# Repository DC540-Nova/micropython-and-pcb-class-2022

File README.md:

# MicroPython & PCB Class 2022
MicroPython & PCB Class 2022 repo.

<br>

# Prerequisites (ideally before class starts)
* Install Thonny
* Install Kicad 6 -- follow through their installation procedure to make sure you have symbol and footprint libraries. Hit us up in the Discord class channel if you have any issues.

# Parts (Amazon links are Amazon Associate Links, purchasing through these links Benefits DC540)
[Raspberry Pi Pico w/ Pre-Soldered Headers](https://www.amazon.com/Raspberry-Microcontroller-Development-Dual-Core-Processor/dp/B08TN4VLN7?crid=13SC9RF6AR4FG&keywords=raspberry+pi+pico&qid=1661530301&sprefix=raspberry+pi+pico,aps,98&sr=8-11&linkCode=sl1&tag=540baab-20&linkId=3f7a7fddf92c960705a15b6c127fc1d6&language=en_US&ref_=as_li_ss_tl)<br>
[Breadboard & Wires](https://amzn.to/3LBkxHO) [updated link 2022-09-21] <br>
[Push Buttons](https://www.amazon.com/QTEATAK-Momentary-Tactile-Button-Switch/dp/B07VSNN9S2?crid=397PJODSKLVT8&keywords=5mm+4-post+push+button&qid=1661556619&sprefix=5mm+4-post+push+button,aps,43&sr=8-8&linkCode=sl1&tag=540baab-20&linkId=967552c52062183be0af39d3209359f7&language=en_US&ref_=as_li_ss_tl)<br>
[NeoPixel Ring](https://www.amazon.com/Stemedu-WS2812B-Integrated-Drivers-Raspberry/dp/B09MHX78WL?crid=2C4AG9RZT6W9J&keywords=neopixel%2Bring&qid=1661976974&s=hi&sprefix=neopixel%2Bring,tools,54&sr=1-4&th=1&linkCode=sl1&tag=540baab-20&linkId=e2077e5200e67458f7c71553bfc39023&language=en_US&ref_=as_li_ss_tl)<br>
[SSD1306 Display](https://www.amazon.com/HiLetgo-Serial-128X64-Display-Color/dp/B06XRBTBTB?crid=H7MU2U37O3GF&keywords=ssd1306+oled+display&qid=1661556692&sprefix=ssd1306,aps,72&sr=8-9&linkCode=sl1&tag=540baab-20&linkId=b2929946a48e2fb56bf9353001b6bba1&language=en_US&ref_=as_li_ss_tl)<br>

# Lesson Playlist
### [YouTube](https://youtube.com/playlist?list=PLvHfoRwREM9NEh0unEx78AdT5MzEejzg7)

<br>

# License
[Apache License, Version 2.0](https://www.apache.org/licenses/LICENSE-2.0)

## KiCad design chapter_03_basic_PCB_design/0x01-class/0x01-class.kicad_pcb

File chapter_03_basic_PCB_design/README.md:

# MicroPython & PCB Class 2022
MicroPython & PCB Class 2022 Chapter 3 - Basic PCB Design.

<br>

## PREREQUISITE - WATCH LESSON 3 [video](https://www.youtube.com/watch?v=9N72FxIyK1k)

<br>

# STEP 1: Create Project
```bash
file
new project
0x01-class
SAVE
```

# STEP 2: Open Schematic
```bash
double-click 0x01-class-kicad_sch
visit https://github.com/ncarandini/KiCad-RP-Pico
code
download ZIP
(unzip file)
```

# STEP 3: Add Pico Footprint To SCH
```bash
create, delete and edit footprints
file
add library
global
KiCad-RP-Pico-main
RP-Pico Libraries
MCU_RapsberryPi_and_Boards.kicad_sym
select folder
```

# STEP 4: Place Pico Footprint
```bash
place
add symbol [a]
(search) Pico
MCU_RapsberryPi_and_Boards
Pico
OK
```

# STEP 5: Place NeoPixel Footprints
```bash
place
add symbol [a]
(search) WS2812B
LED
WS2812B
OK
(hover over WS2812B, click and CTRL-C and CTRL-V)
(repeat 5x and place)
```

# STEP 6: Add A Power Port & Net Label
```bash
add a power port [p]
(search) +3V3
power
+3V3
OK
add a net label [l]
3V3
OK
(attach to wire hole on +3V3)
(click 3V3)
(click [m])
(attach to 3V3 on Pico)
(delete +3V3 and optional wire)
(hover over 3V3 on Pico, click and CTRL-C and CTRL-V)
(attach to wire hole on 1st WS2812B's VDD and repeat 5x for other WS2812B's)
```

# STEP 7: Add GND Net Label & Wire Up GND's To Neopixels
```bash
add a net label [l]
GND
OK
(attach to GND Pin 38 on Pico)
(hover over GND on Pico, click and CTRL-C and CTRL-V)
(attach to other GND pins on Pico, [r] when necessary)
(hover over any GND on Pico, click and CTRL-C and CTRL-V)
(attach to wire hole on 1st WS2812B's VSS and repeat 5x for other WS2812B's)
```

# STEP 8: Add NeoPixel Net Label & Wire Up Neopixels
```bash
add a net label [l]
NP
OK
(attach to GPIO18 on Pico)
(hover over NP and CTRL-C and CTRL-V 1x)
(hover over NP and CTRL-C and CTRL-V 1x)
(type [r] 2x and attach to DIN hole on 1st WS2812B)
add a wire [w]
(attach to DOUT on 1st WS2812B and connect to DIN on 2nd WS2812B)
(repeat process to remainder of WS2812B's)
```

# STEP 9: Add Pico Footprint To PCB
```bash
open PCB in board editor
update PCB with changes made to schematic [F8]
annotate
update PCB
close
create, delete and edit footprints
file
add library
global
KiCad-RP-Pico-main
RP-Pico Libraries
MCU_RapsberryPi_and_Boards.pretty
select folder
(search) RPi_Pico_SMD_TH
(double-click)
(save)
(X)
```

# STEP 10: Place Pico Footprint
```bash
open schematic in eeschema
(right-click inside empty area in Pico and click properties)
(click footprint RPi_Pico-RPi_Pico_SMD_TH and click bookshelf icon and ok)
(search) MCU_RaspberryPi_and_Boards
(double-click) RPi_Pico_SMD_TH
OK
open PCB in board editor
update PCB with changes made to schematic [F8]
update PCB
close
```

# STEP 11: Connect & Arrage Neopixels 
```bash
(arrange WS2812B's appropriately where GP18 connects to 1st WS2812B's NP, etc)
([r] when necessary)
(*NOTE: click in black area in center of WS2812B to move whole unit rather than pieces*)
edit board setup including layers, design rules and various defaults
design rules
net classes
+
PWR
track width
0.35 mm
net
/3V3
net class
PWR
/GND
net class
PWR
OK
```

# STEP 12: Route Tracks & Check Design
```
route tracks [x]
(click GP18 on Pico and conect to NP on first WS2812B)
(connect 2nd to 3rd, etc)
(click 3V3 on Pico and connect to 3V3 on first WS2812B)
(connect 2nd to 3rd, etc)
edge cuts
draw a rectangle
(draw box around circuit)
F.Cu
add a filled zone [CTRL-SHIFT-Z]
(click) /GND
ok
(draw ouside board trace, click upper left and drag and click as appropriate)
(double-click to finish)
fill all zones [b]
show the design rules checker window
run DRC
close
```

<br>

# License
[Apache License, Version 2.0](https://www.apache.org/licenses/LICENSE-2.0)

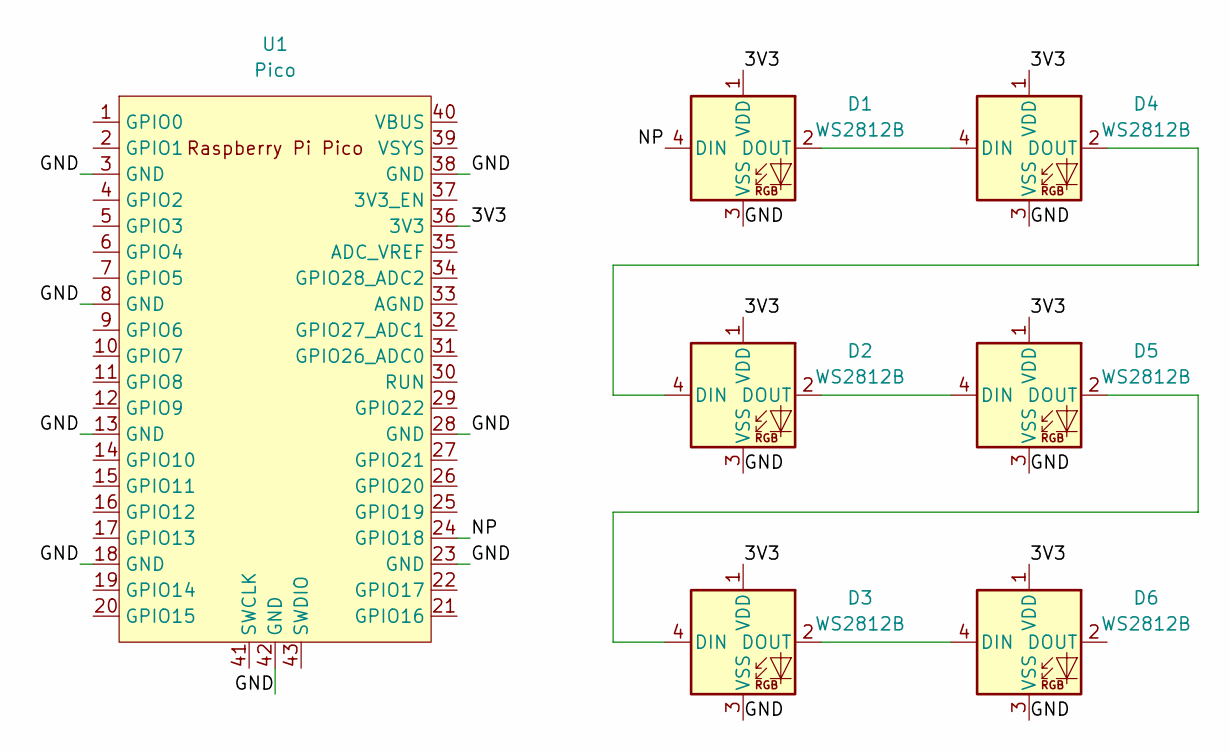
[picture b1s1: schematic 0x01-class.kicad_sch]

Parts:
D1, D2, D3, D4, D5, D6: WS2812B; LED_WS2812B_PLCC4_5.0x5.0mm_P3.2mm
U1: Pico; RPi_Pico_SMD_TH

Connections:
/3V3: D1.1 (VDD), D2.1 (VDD), D3.1 (VDD), D4.1 (VDD), D5.1 (VDD), D6.1 (VDD), U1.36 (3V3)
/GND: D1.3 (VSS), D2.3 (VSS), D3.3 (VSS), D4.3 (VSS), D5.3 (VSS), D6.3 (VSS), U1.3 (GND), U1.8 (GND), U1.13 (GND), U1.18 (GND), U1.23 (GND), U1.28 (GND), U1.38 (GND), U1.42 (GND)
/NP: D1.4 (DIN), U1.24 (GPIO18)
unnamed: D1.2 (DOUT), D4.4 (DIN)
unnamed: D2.2 (DOUT), D5.4 (DIN)
unnamed: D2.4 (DIN), D4.2 (DOUT)
unnamed: D3.2 (DOUT), D6.4 (DIN)
unnamed: D3.4 (DIN), D5.2 (DOUT)

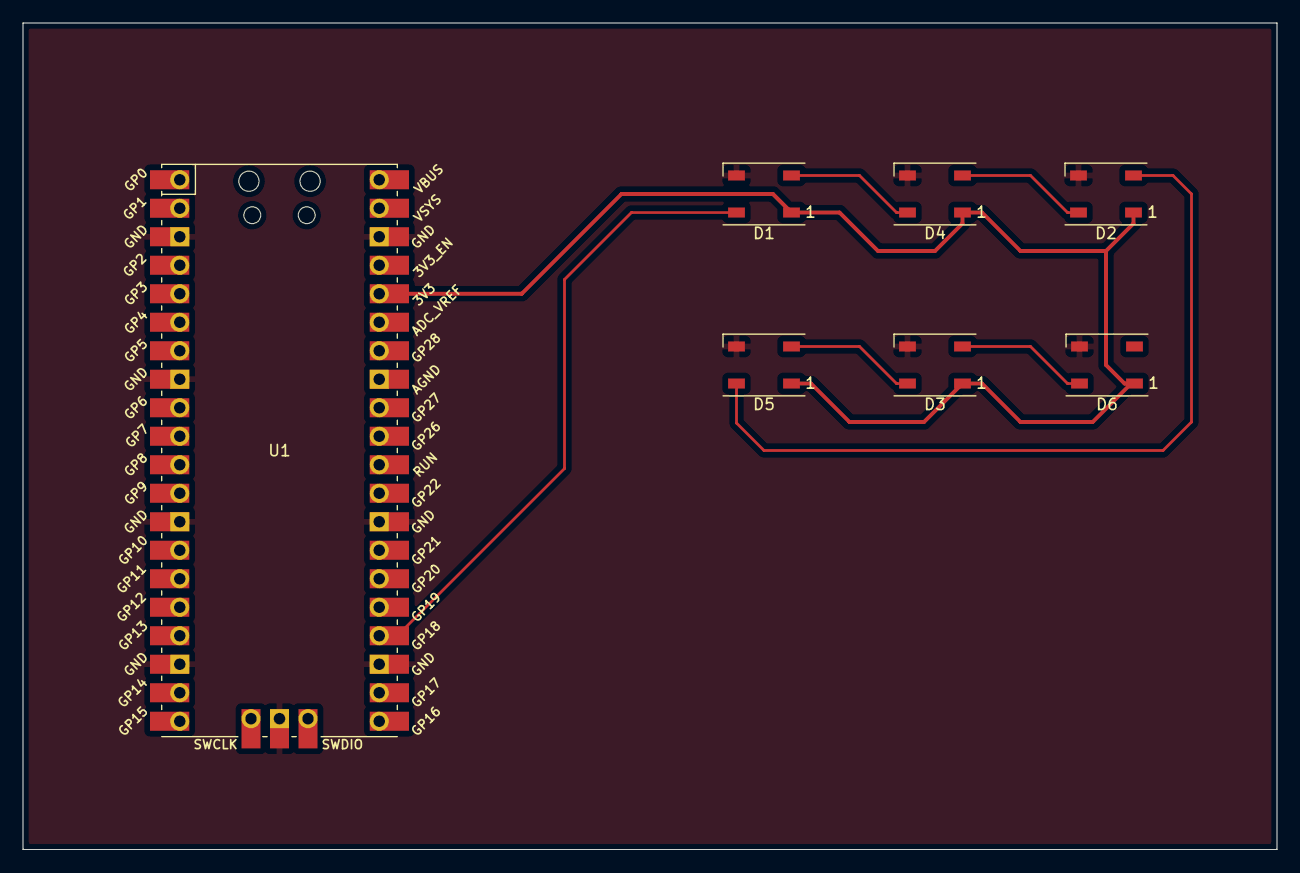
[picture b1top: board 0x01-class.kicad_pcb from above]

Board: 2 copper layers, 111.8 x 73.7 mm, 7 parts (0 on the bottom side), 8 nets.

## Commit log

2022-08-28 Added files for Chapter 1
2022-10-08 Added files for chapter_01
2022-10-22 Added files for Chapter 3
